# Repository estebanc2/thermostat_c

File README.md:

# Thermostat

## Summary

This repository describes how to build a "thermostat" to make yogurt keeping temp around 40 °C turning on and off a heater source.

This is an open-source software and hardware project. The circuit diagram and board layout design, the programs in C for the ESP 8266 microcontroller are made available under the GPLv3 license. See the file LICENSE.txt in the same directory along with this file.

## Hardware

The hardware design is quite simple; just what the Espressif 8266 module needs to operate:

- 5V @ 200mA power supply
- 3.3V regulator
- One 220VAC @ 6A relays to control the load(s)
- DS18B20 temperature sensor(HW/DS18B20.pdf)

The following pictures show the schematics, boards, and switches with all their elements.

The HW folder in this repository contains documents needed to order boards from [JLCPCB](https://jlcpcb.com/) and Kikad projects for simple and double switches.

## Software

There is a simple periodic task that keep the switch on until 41°C, the upper side of the histeresis and turn it on again under 39°C, the lowwer side of the histeresis.
To read the temperature I used other open source project: [one_wire](https://github.com/estebanc2/one_wire)

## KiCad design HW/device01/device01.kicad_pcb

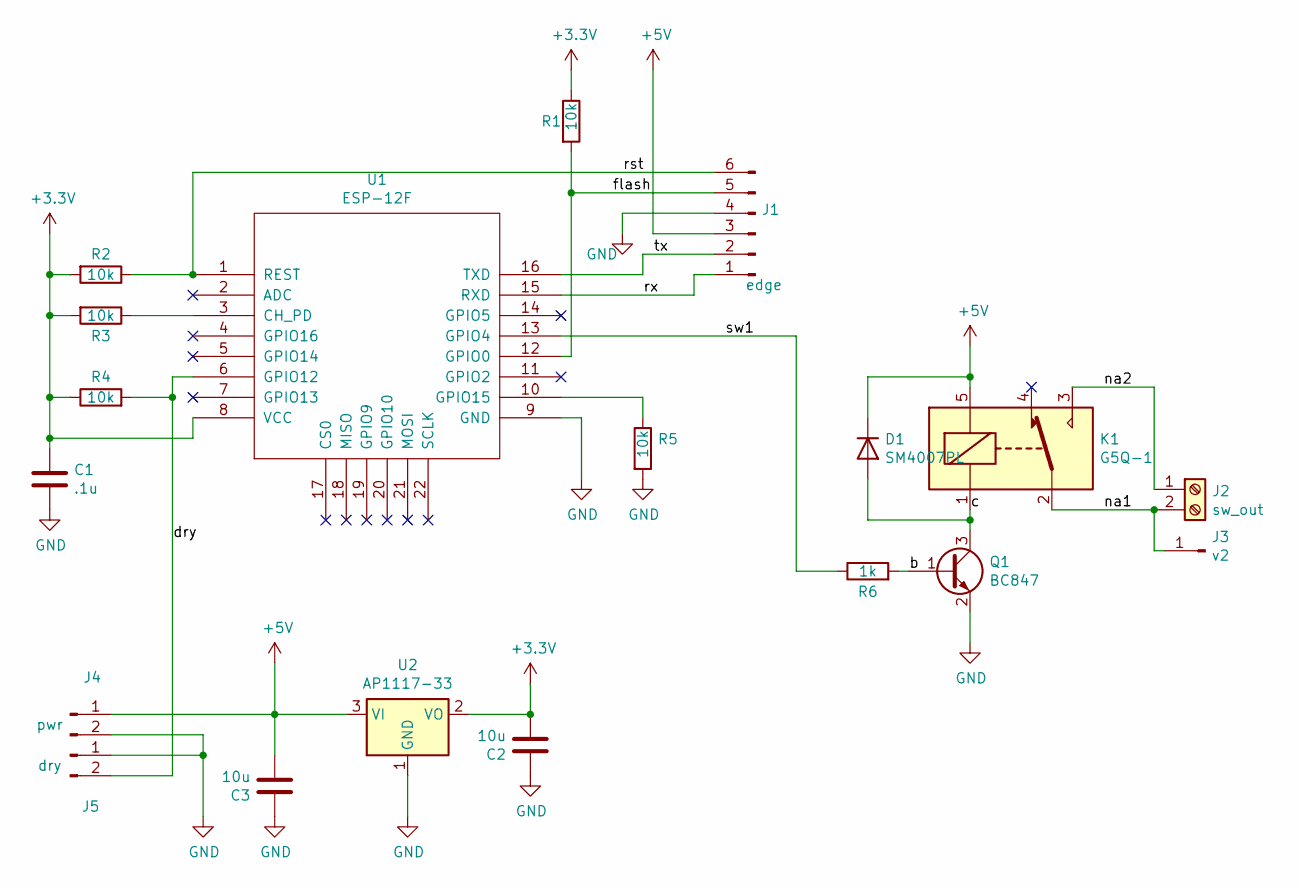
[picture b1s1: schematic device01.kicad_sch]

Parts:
C1: .1u; C_0402_1005Metric
C2, C3: 10u; C_1206_3216Metric
D1: SM4007PL
J1: edge; edge6
J2: sw_out; TerminalBlock_RND_205-00232_1x02_P5.08mm_Horizontal
J3: v2; 1wirehole
J4: pwr; PinHeader_1x02_P2.54mm_Vertical
J5: dry; PinHeader_1x02_P2.54mm_Vertical
K1: G5Q-1; Relay_SPDT_Omron-G5Q-1
Q1: BC847; SOT-23
R1, R2, R3, R4, R5: 10k; C_0402_1005Metric
R6: 1k; C_0402_1005Metric
U1: ESP-12F; ESP-12E_SMD
U2: AP1117-33; SOT-223-3_TabPin2

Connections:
+3V3: C1.1, C2.2, R1.1, R2.2, R3.2, R4.1, U1.8 (VCC), U2.2 (VO)
+5V: C3.2, D1.1 (K), J1.3, J4.1, K1.5, U2.3 (VI)
/b: Q1.1 (B), R6.2
/c: D1.2 (A), K1.1, Q1.3 (C)
/dry: J5.2, R4.2, U1.6 (GPIO12)
/flash: J1.5, R1.2, U1.12 (GPIO0)
/na1: J2.2, J3.1, K1.2
/na2: J2.1, K1.3
/rst: J1.6, R2.1, U1.1 (REST)
/rx: J1.1, U1.15 (RXD)
/sw1: R6.1, U1.13 (GPIO4)
/tx: J1.2, U1.16 (TXD)
GND: C1.2, C2.1, C3.1, J1.4, J4.2, J5.1, Q1.2 (E), R5.2, U1.9 (GND), U2.1 (GND)
unnamed: R3.1, U1.3 (CH_PD)
unnamed: R5.1, U1.10 (GPIO15)

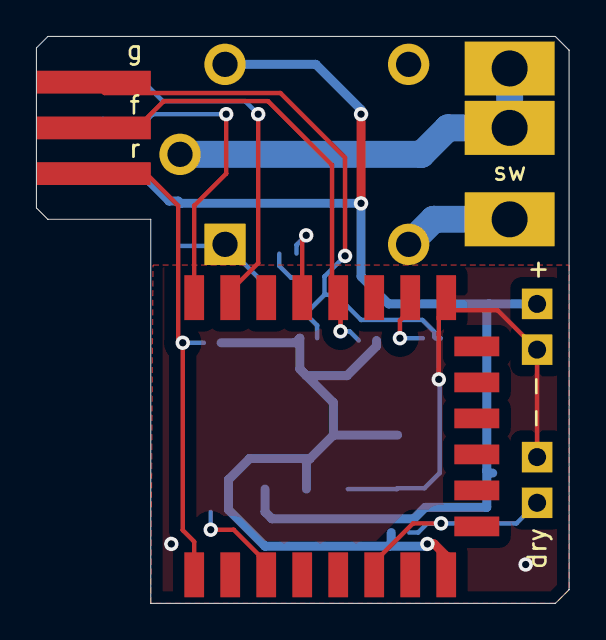
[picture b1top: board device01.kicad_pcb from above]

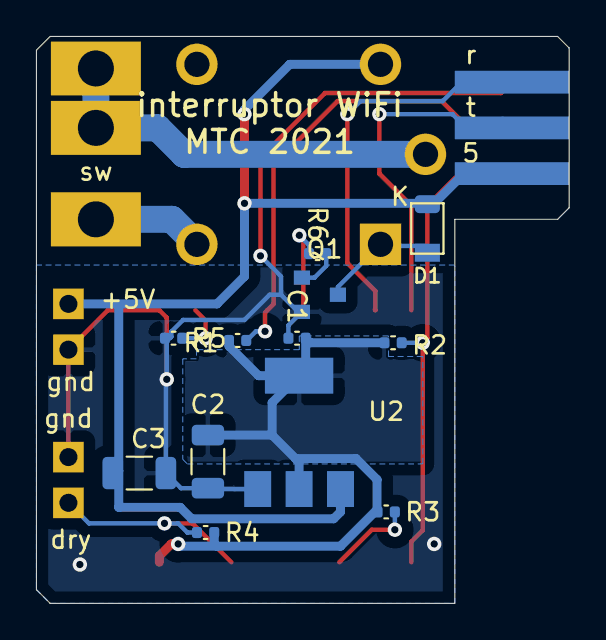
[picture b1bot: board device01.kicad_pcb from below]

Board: 2 copper layers, 29.6 x 31.5 mm, 19 parts (13 on the bottom side), 15 nets.

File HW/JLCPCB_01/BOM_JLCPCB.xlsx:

Comment | Designator | Footprint | LCSC part Number
100nF | C1 | 0402 | C60474
10uF | C2,C3 | 1206 | C92765
SM4007PL | D1 | SOD-123FL | C64898
10K | R1,R2,R3,R4,R5 | 0402 | C60489
1K | R6 | 0402 | C105637
AP1117-33 | U2 | SOT-223 | C173386
BC847 | Q1 | SOT-23 | C57668

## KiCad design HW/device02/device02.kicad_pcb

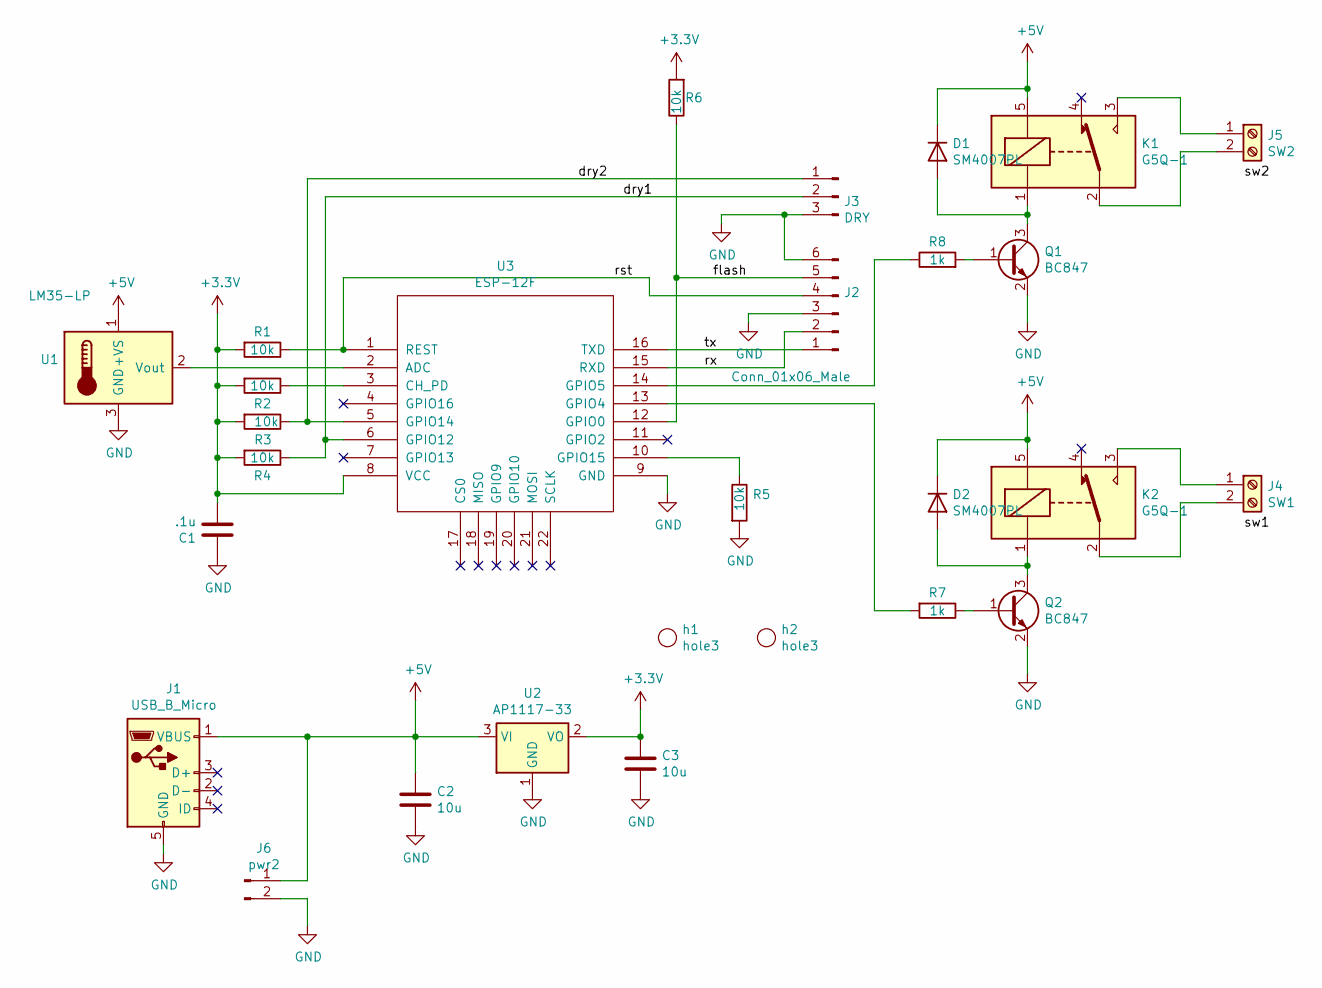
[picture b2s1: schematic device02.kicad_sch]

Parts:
C1: .1u; C_0402_1005Metric
C2, C3: 10u; C_1206_3216Metric
D1, D2: SM4007PL
J1: USB_B_Micro; micro_usb_b_dual
J2: Conn_01x06_Male; edge6
J3: DRY; PinHeader_1x03_P2.54mm_Vertical
J4: SW1; TerminalBlock_RND_205-00232_1x02_P5.08mm_Horizontal
J5: SW2; TerminalBlock_RND_205-00232_1x02_P5.08mm_Horizontal
J6: pwr2; PinHeader_1x02_P2.54mm_Vertical
K1, K2: G5Q-1; Relay_SPDT_NT78_C_S_0.6
Q1, Q2: BC847; SOT-23
R1, R2, R3, R4, R5, R6: 10k; C_0402_1005Metric
R7, R8: 1k; C_0402_1005Metric
U1: LM35-LP; TO-92
U2: AP1117-33; SOT-223-3_TabPin2
U3: ESP-12F; ESP-12E_SMD
h1, h2: hole3

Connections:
+3V3: C1.2, C3.1, R1.2, R2.2, R3.2, R4.2, R6.2, U2.2 (VO), U3.8 (VCC)
+5V: C2.1, D1.1 (K), D2.1 (K), J1.1 (VBUS), J6.1, K1.5, K2.5, U1.1 (+VS), U2.3 (VI)
/dry1: J3.2, R4.1, U3.6 (GPIO12)
/dry2: J3.1, R3.1, U3.5 (GPIO14)
/flash: J2.5, R6.1, U3.12 (GPIO0)
/rst: J2.4, R1.1, U3.1 (REST)
/rx: J2.2, U3.15 (RXD)
/tx: J2.1, U3.16 (TXD)
GND: C1.1, C2.2, C3.2, J1.5 (GND), J2.3, J2.6, J3.3, J6.2, Q1.2 (E), Q2.2 (E), R5.2, U1.3 (GND), U2.1 (GND), U3.9 (GND)
unnamed: D1.2 (A), K1.1, Q1.3 (C)
unnamed: D2.2 (A), K2.1, Q2.3 (C)
unnamed: J4.1, K2.3
unnamed: J4.2, K2.2
unnamed: J5.1, K1.3
unnamed: J5.2, K1.2
unnamed: Q1.1 (B), R8.2
unnamed: Q2.1 (B), R7.1
unnamed: R2.1, U3.3 (CH_PD)
unnamed: R5.1, U3.10 (GPIO15)
unnamed: R7.2, U3.13 (GPIO4)
unnamed: R8.1, U3.14 (GPIO5)
unnamed: U1.2 (Vout), U3.2 (ADC)

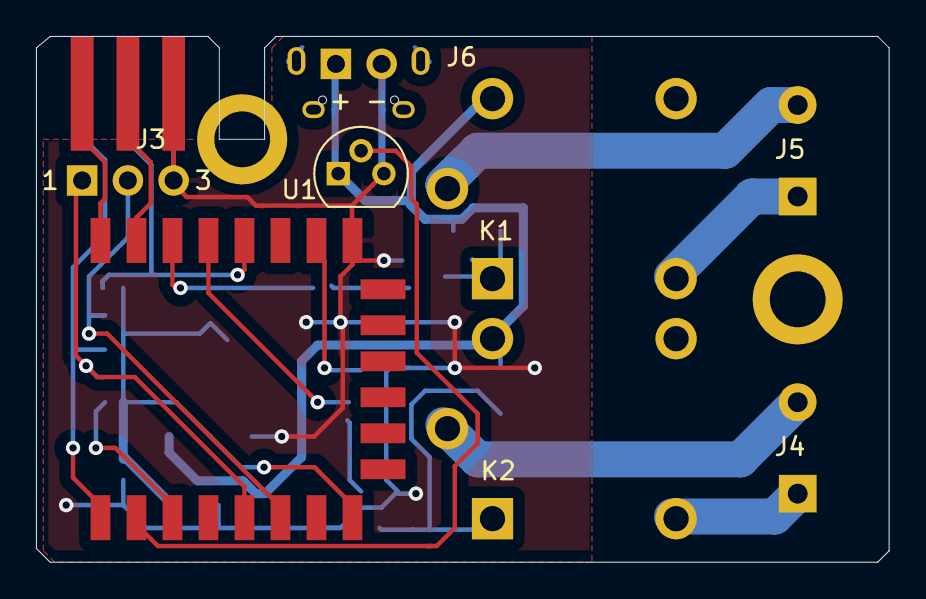
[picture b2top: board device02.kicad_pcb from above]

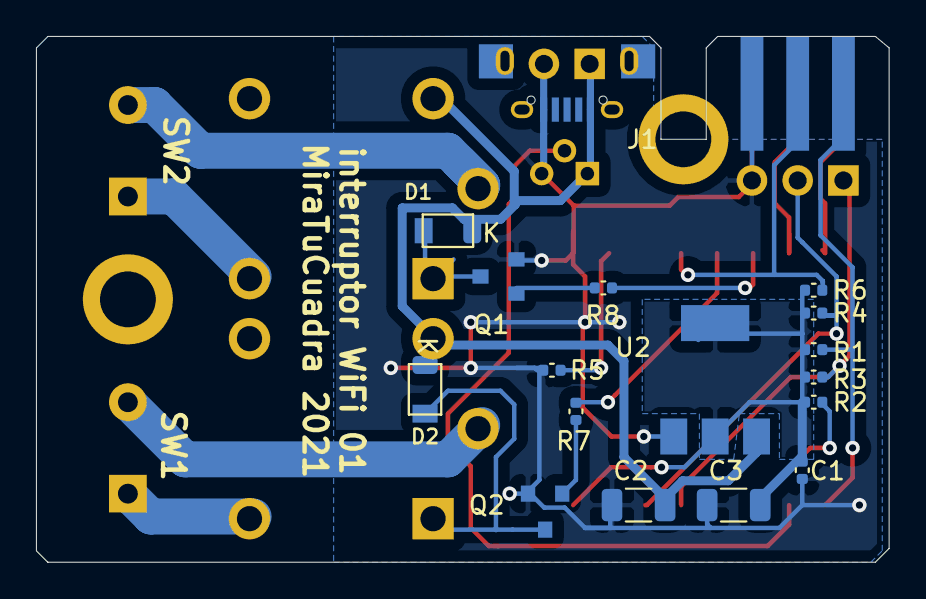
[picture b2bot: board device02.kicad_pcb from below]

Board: 2 copper layers, 47.4 x 29.2 mm, 28 parts (17 on the bottom side), 22 nets.

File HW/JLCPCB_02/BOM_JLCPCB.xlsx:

Comment | Designator | Footprint | LCSC part Number
100nF | C1 | 0402 | C60474
10uF | C2,C3 | 1206 | C92765
SM4007PL | D1, D2 | SOD-123FL | C64898
10K | R1,R2,R3,R4,R5, R6 | 0402 | C60489
1K | R7, R8 | 0402 | C105637
AP1117-33 | U2 | SOT-223 | C173386
BC847 | Q1,Q2 | SOT-23 | C57668
10118194-0001LF | J1 | USB-B-MICRO | C132563

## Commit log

2025-07-06 first
2025-07-06 cleanup
2025-07-06 anda todo 5/5
2025-07-12 branch para usar mi nueva lib
2025-07-12 funciona
